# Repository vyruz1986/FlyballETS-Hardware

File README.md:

## FlyballETS-Hardware

The FlyballETS-Hardware project is a subproject of the [Flyball ETS project](https://www.sparkydevices.com/tag/flyball-ets/).
It contains the designs for the electronic hardware which is required to build the Flyball-ETS project.

## Design Files

The design files are in KiCAD format, and consist of several files:
* FlyballETS-Board.sch/kicad_pcb: Schematic and board file for the PCB of Flyball ETS
* FlyballETS-Board-BOM.txt: Bill of materials used to know which components to order and where to solder them on the board

These files can be used by people who want to improve or change the design.

## Export Files
`Exports/FlyballETS-Board-BRD/SCH.png` are picture exports of the design files so people can view them without needing to install EAGLE

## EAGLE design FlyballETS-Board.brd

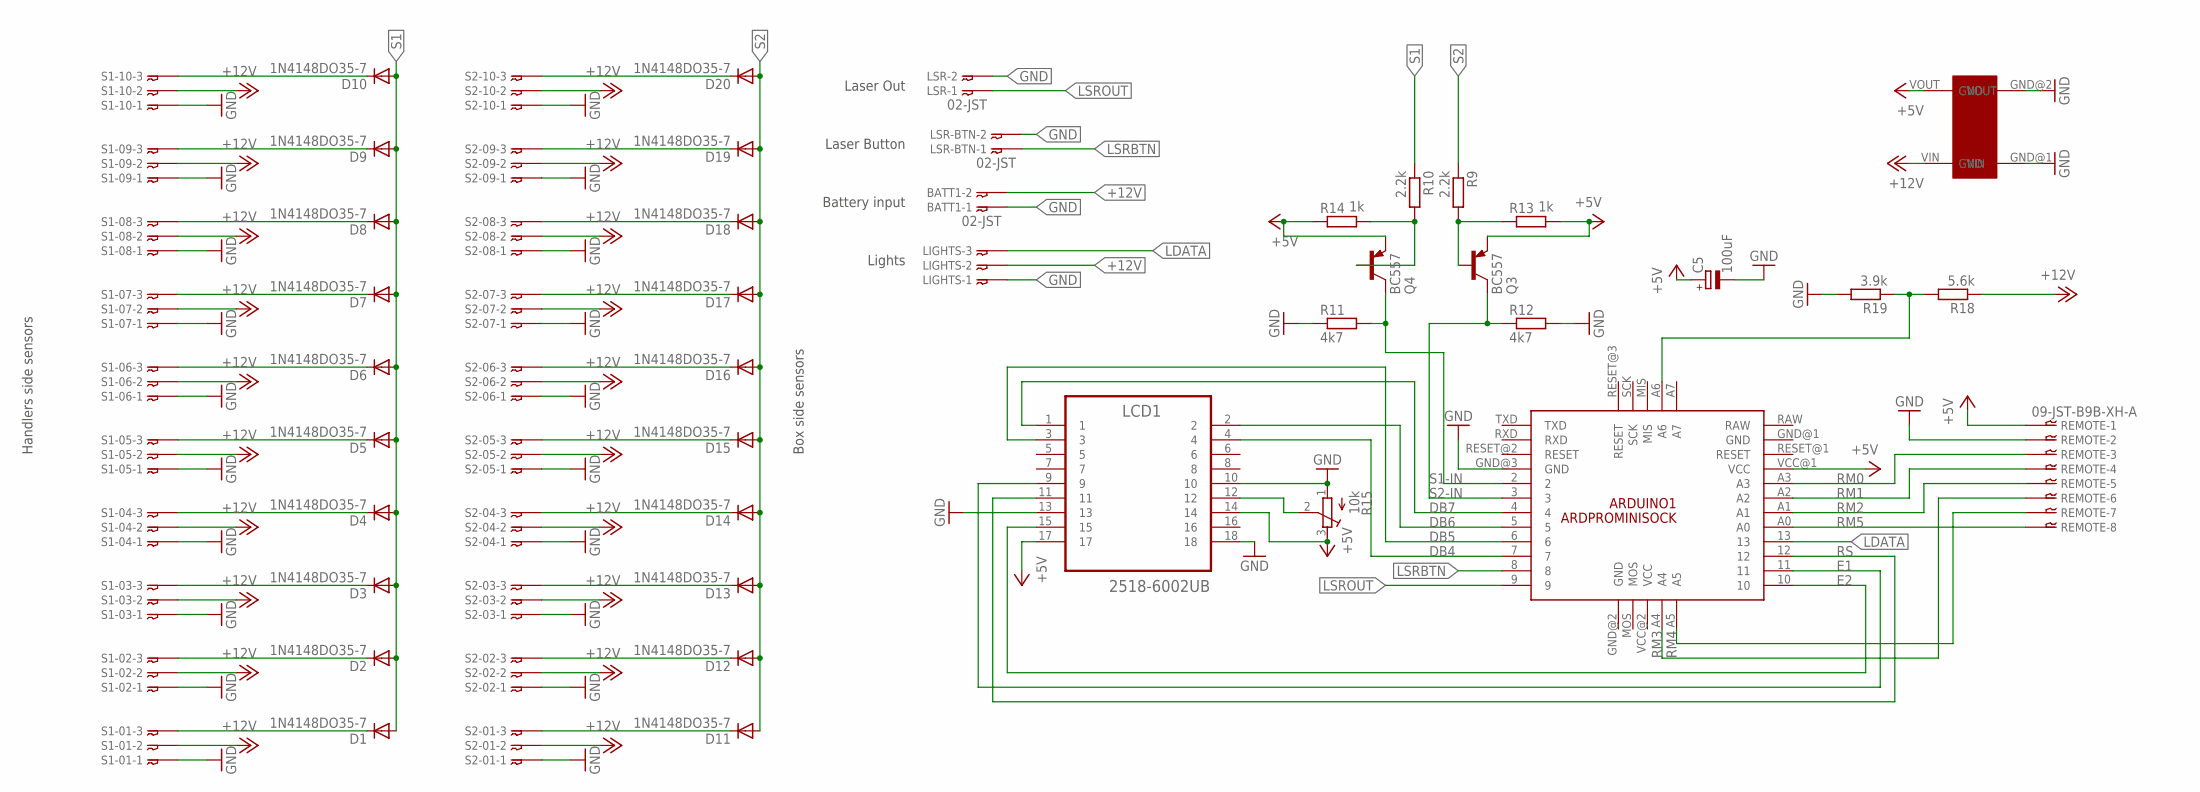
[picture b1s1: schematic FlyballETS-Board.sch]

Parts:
ARDUINO1: ARDPROMINISOCK
BATT1: 02-JST; B2B-XH
C5: 100uF; E2,5-6E
D1, D2, D3, D4, D5, D6, D7, D8, D9, D10, D11, D12, D13, D14, D15, D16, D17, D18, D19, D20: 1N4148DO35-7; DO35-7
LCD1: 2518-6002UB; 3M_2518-6002UB
LIGHTS: 03-JST-B3B-XH-A; B3B-XH
LSR: 02-JST; B2B-XH
LSR-BTN: 02-JST; B2B-XH
Q3, Q4: BC557; TO92
R9, R10: 2.2k; 0207/10
R11, R12: 4k7; 0207/10
R13, R14: 1k; 0207/10
R15: 10k; RTRIM3339P
R18: 5.6k; 0207/10
R19: 3.9k; 0207/10
REMOTE: 09-JST-B9B-XH-A; B9B-XH
S1-01, S1-02, S1-03, S1-04, S1-05, S1-06, S1-07, S1-08, S1-09, S1-10, S2-01, S2-02, S2-03, S2-04, S2-05, S2-06, S2-07, S2-08, S2-09, S2-10: 03-JST-B3B-XH-A; B3B-XH
U$2: LM2596-BOARD

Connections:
+5V: ARDUINO1.VCC@1 (VCC), C5.+, LCD1.14, LCD1.17, Q3.1 (E), Q4.1 (E), R13.2, R14.1, R15.3 (E), REMOTE.P$1, U$2.VOUT
+12V: BATT1.P$2, LIGHTS.P$2, R18.1, S1-01.P$2, S1-02.P$2, S1-03.P$2, S1-04.P$2, S1-05.P$2, S1-06.P$2, S1-07.P$2, S1-08.P$2, S1-09.P$2, S1-10.P$2, S2-01.P$2, S2-02.P$2, S2-03.P$2, S2-04.P$2, S2-05.P$2, S2-06.P$2, S2-07.P$2, S2-08.P$2, S2-09.P$2, S2-10.P$2, U$2.VIN
DB4: ARDUINO1.7, LCD1.4
DB5: ARDUINO1.6, LCD1.3
DB6: ARDUINO1.5, LCD1.2
DB7: ARDUINO1.4, LCD1.1
E1: ARDUINO1.11, LCD1.9
E2: ARDUINO1.10, LCD1.15
GND: ARDUINO1.GND@3 (GND), BATT1.P$1, C5.-, LCD1.10, LCD1.13, LCD1.18, LIGHTS.P$1, LSR.P$2, LSR-BTN.P$2, R11.1, R12.2, R15.1 (A), R19.2, REMOTE.P$2, S1-01.P$1, S1-02.P$1, S1-03.P$1, S1-04.P$1, S1-05.P$1, S1-06.P$1, S1-07.P$1, S1-08.P$1, S1-09.P$1, S1-10.P$1, S2-01.P$1, S2-02.P$1, S2-03.P$1, S2-04.P$1, S2-05.P$1, S2-06.P$1, S2-07.P$1, S2-08.P$1, S2-09.P$1, S2-10.P$1, U$2.GND@1 (GND), U$2.GND@2 (GND)
LDATA: ARDUINO1.13, LIGHTS.P$3
LSRBTN: ARDUINO1.8, LSR-BTN.P$1
LSROUT: ARDUINO1.9, LSR.P$1
unnamed: Q3.2 (B), R9.2, R13.1
unnamed: Q4.2 (B), R10.2, R14.2
unnamed: LCD1.12, R15.2 (S)
unnamed: D10.C, S1-10.P$3
unnamed: D9.C, S1-09.P$3
unnamed: D8.C, S1-08.P$3
unnamed: D7.C, S1-07.P$3
unnamed: D6.C, S1-06.P$3
unnamed: D5.C, S1-05.P$3
unnamed: D4.C, S1-04.P$3
unnamed: D3.C, S1-03.P$3
unnamed: D2.C, S1-02.P$3
unnamed: D1.C, S1-01.P$3
unnamed: D20.C, S2-10.P$3
unnamed: D19.C, S2-09.P$3
unnamed: D18.C, S2-08.P$3
unnamed: D17.C, S2-07.P$3
unnamed: D16.C, S2-06.P$3
unnamed: D15.C, S2-05.P$3
unnamed: D14.C, S2-04.P$3
unnamed: D13.C, S2-03.P$3
unnamed: D12.C, S2-02.P$3
unnamed: D11.C, S2-01.P$3
RM0: ARDUINO1.A3, REMOTE.P$3
RM1: ARDUINO1.A2, REMOTE.P$4
RM2: ARDUINO1.A1, REMOTE.P$5
RM3: ARDUINO1.A4, REMOTE.P$6
RM4: ARDUINO1.A5, REMOTE.P$7
RM5: ARDUINO1.A0, REMOTE.P$8
RS: ARDUINO1.12, LCD1.11
S1: D1.A, D2.A, D3.A, D4.A, D5.A, D6.A, D7.A, D8.A, D9.A, D10.A, R10.1
S1-IN: ARDUINO1.2, Q4.3 (C), R11.2
S2: D11.A, D12.A, D13.A, D14.A, D15.A, D16.A, D17.A, D18.A, D19.A, D20.A, R9.1
S2-IN: ARDUINO1.3, Q3.3 (C), R12.1
VSENS: ARDUINO1.A6, R18.2, R19.1

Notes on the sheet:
Battery input
Handlers side sensors
Box side sensors
Laser Out
Laser Button
Lights

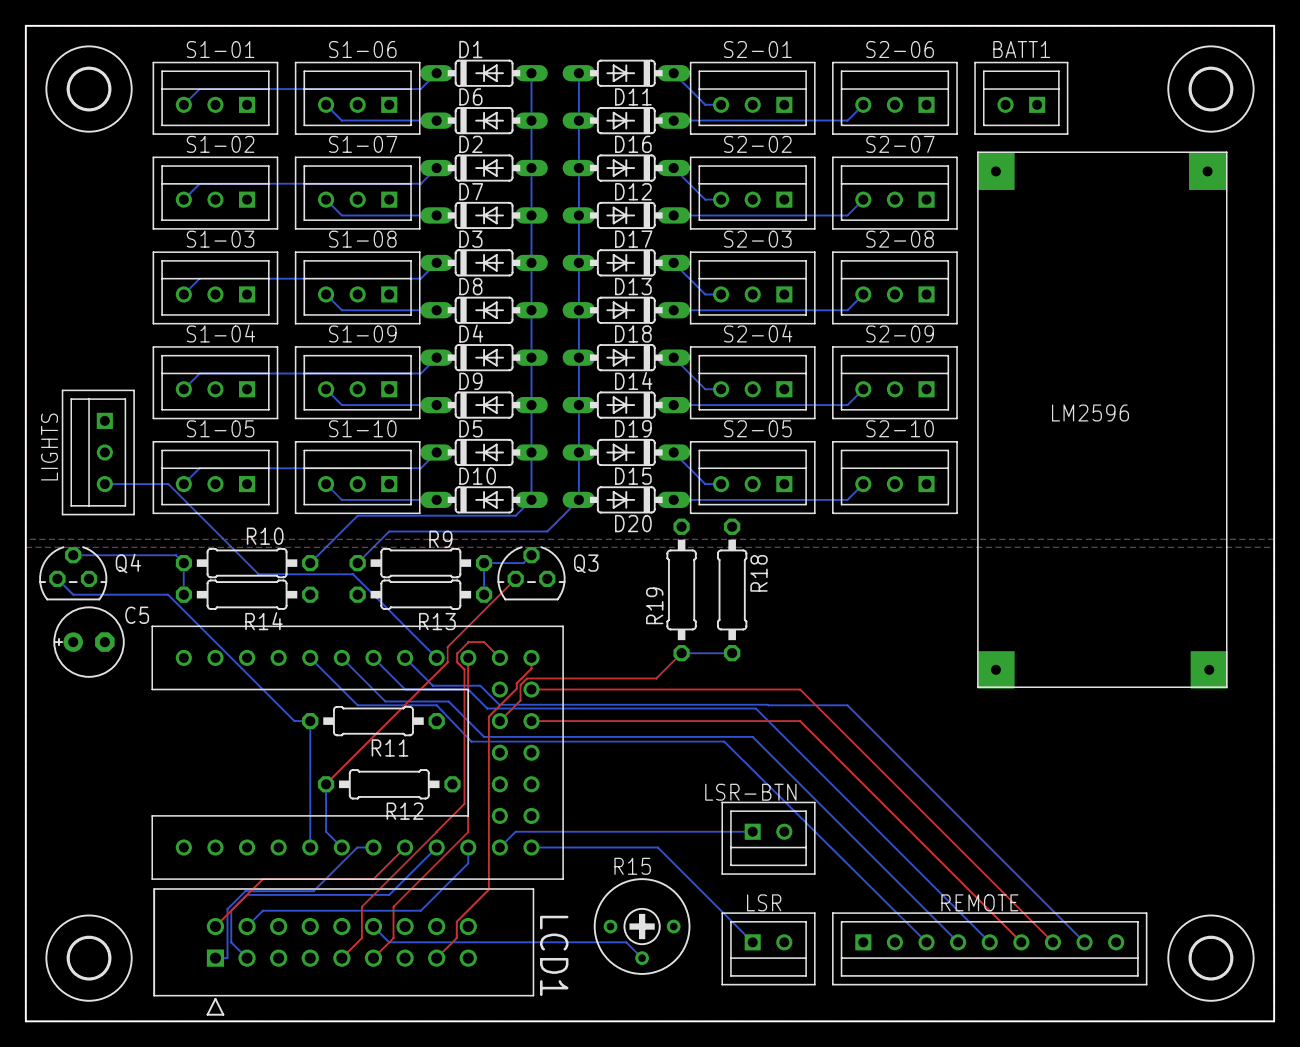
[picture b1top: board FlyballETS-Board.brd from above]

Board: 2 copper layers, 100.3 x 80.0 mm, 64 parts (0 on the bottom side), 47 nets.

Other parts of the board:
U$1, U$3, U$4, U$5: 3,2

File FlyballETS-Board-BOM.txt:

Partlist exported from C:/Workspaces/personal/FlyballETS-Hardware/FlyballETS-Board.sch at 25/10/2017 10:56

Part     Value           Device          Package        Description                          
ARDUINO1 ARDPROMINISOCK  ARDPROMINISOCK  ARDPROMINISOCK                                      
BATT1    02-JST          02-JST          B2B-XH         JST CONNECTOR                        
C5       100uF           CPOL-EUE2,5-6E  E2,5-6E        POLARIZED CAPACITOR, European symbol 
D1       1N4148DO35-7    1N4148DO35-7    DO35-7         DIODE                                
D2       1N4148DO35-7    1N4148DO35-7    DO35-7         DIODE                                
D3       1N4148DO35-7    1N4148DO35-7    DO35-7         DIODE                                
D4       1N4148DO35-7    1N4148DO35-7    DO35-7         DIODE                                
D5       1N4148DO35-7    1N4148DO35-7    DO35-7         DIODE                                
D6       1N4148DO35-7    1N4148DO35-7    DO35-7         DIODE                                
D7       1N4148DO35-7    1N4148DO35-7    DO35-7         DIODE                                
D8       1N4148DO35-7    1N4148DO35-7    DO35-7         DIODE                                
D9       1N4148DO35-7    1N4148DO35-7    DO35-7         DIODE                                
D10      1N4148DO35-7    1N4148DO35-7    DO35-7         DIODE                                
D11      1N4148DO35-7    1N4148DO35-7    DO35-7         DIODE                                
D12      1N4148DO35-7    1N4148DO35-7    DO35-7         DIODE                                
D13      1N4148DO35-7    1N4148DO35-7    DO35-7         DIODE                                
D14      1N4148DO35-7    1N4148DO35-7    DO35-7         DIODE                                
D15      1N4148DO35-7    1N4148DO35-7    DO35-7         DIODE                                
D16      1N4148DO35-7    1N4148DO35-7    DO35-7         DIODE                                
D17      1N4148DO35-7    1N4148DO35-7    DO35-7         DIODE                                
D18      1N4148DO35-7    1N4148DO35-7    DO35-7         DIODE                                
D19      1N4148DO35-7    1N4148DO35-7    DO35-7         DIODE                                
D20      1N4148DO35-7    1N4148DO35-7    DO35-7         DIODE                                
LCD1     2518-6002UB     2518-6002UB     3M_2518-6002UB                                      
LIGHTS   03-JST-B3B-XH-A 03-JST-B3B-XH-A B3B-XH         JST CONNECTOR                        
LSR      02-JST          02-JST          B2B-XH         JST CONNECTOR                        
LSR-BTN  02-JST          02-JST          B2B-XH         JST CONNECTOR                        
Q3       BC557           BC557           TO92           PNP Transistor                       
Q4       BC557           BC557           TO92           PNP Transistor                       
R9       2.2k            R-EU_0207/10    0207/10        RESISTOR, European symbol            
R10      2.2k            R-EU_0207/10    0207/10        RESISTOR, European symbol            
R11      4k7             R-EU_0207/10    0207/10        RESISTOR, European symbol            
R12      4k7             R-EU_0207/10    0207/10        RESISTOR, European symbol            
R13      1k              R-EU_0207/10    0207/10        RESISTOR, European symbol            
R14      1k              R-EU_0207/10    0207/10        RESISTOR, European symbol            
R15      10k             R-TRIMM3339P    RTRIM3339P     Trimm resistor                       
R18      5.6k            R-EU_0207/10    0207/10        RESISTOR, European symbol            
R19      3.9k            R-EU_0207/10    0207/10        RESISTOR, European symbol            
REMOTE   09-JST-B9B-XH-A 09-JST-B9B-XH-A B9B-XH         JST CONNECTOR                        
S1-01    03-JST-B3B-XH-A 03-JST-B3B-XH-A B3B-XH         JST CONNECTOR                        
S1-02    03-JST-B3B-XH-A 03-JST-B3B-XH-A B3B-XH         JST CONNECTOR                        
S1-03    03-JST-B3B-XH-A 03-JST-B3B-XH-A B3B-XH         JST CONNECTOR                        
S1-04    03-JST-B3B-XH-A 03-JST-B3B-XH-A B3B-XH         JST CONNECTOR                        
S1-05    03-JST-B3B-XH-A 03-JST-B3B-XH-A B3B-XH         JST CONNECTOR                        
S1-06    03-JST-B3B-XH-A 03-JST-B3B-XH-A B3B-XH         JST CONNECTOR                        
S1-07    03-JST-B3B-XH-A 03-JST-B3B-XH-A B3B-XH         JST CONNECTOR                        
S1-08    03-JST-B3B-XH-A 03-JST-B3B-XH-A B3B-XH         JST CONNECTOR                        
S1-09    03-JST-B3B-XH-A 03-JST-B3B-XH-A B3B-XH         JST CONNECTOR                        
S1-10    03-JST-B3B-XH-A 03-JST-B3B-XH-A B3B-XH         JST CONNECTOR                        
S2-01    03-JST-B3B-XH-A 03-JST-B3B-XH-A B3B-XH         JST CONNECTOR                        
S2-02    03-JST-B3B-XH-A 03-JST-B3B-XH-A B3B-XH         JST CONNECTOR                        
S2-03    03-JST-B3B-XH-A 03-JST-B3B-XH-A B3B-XH         JST CONNECTOR                        
S2-04    03-JST-B3B-XH-A 03-JST-B3B-XH-A B3B-XH         JST CONNECTOR                        
S2-05    03-JST-B3B-XH-A 03-JST-B3B-XH-A B3B-XH         JST CONNECTOR                        
S2-06    03-JST-B3B-XH-A 03-JST-B3B-XH-A B3B-XH         JST CONNECTOR                        
S2-07    03-JST-B3B-XH-A 03-JST-B3B-XH-A B3B-XH         JST CONNECTOR                        
S2-08    03-JST-B3B-XH-A 03-JST-B3B-XH-A B3B-XH         JST CONNECTOR                        
S2-09    03-JST-B3B-XH-A 03-JST-B3B-XH-A B3B-XH         JST CONNECTOR                        
S2-10    03-JST-B3B-XH-A 03-JST-B3B-XH-A B3B-XH         JST CONNECTOR                        
U$2      LM2596-BOARD    LM2596-BOARD    LM2596-BOARD

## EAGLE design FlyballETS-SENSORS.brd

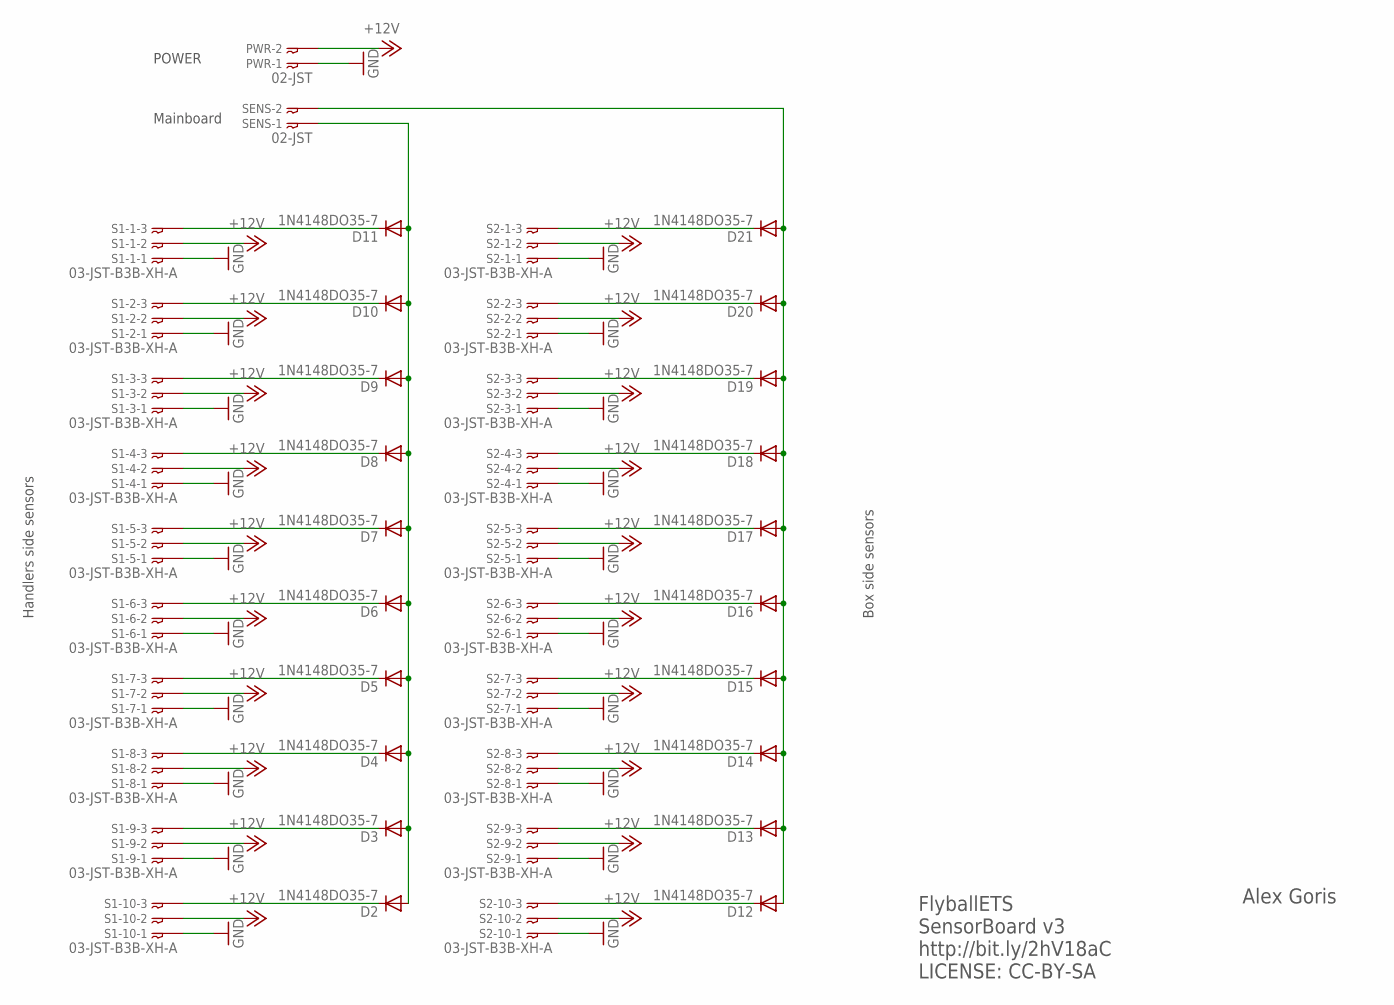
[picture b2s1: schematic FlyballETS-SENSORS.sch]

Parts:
D2, D3, D4, D5, D6, D7, D8, D9, D10, D11, D12, D13, D14, D15, D16, D17, D18, D19, D20, D21: 1N4148DO35-7; DO35-7
PWR: 02-JST; B2B-XH
S1-1, S1-2, S1-3, S1-4, S1-5, S1-6, S1-7, S1-8, S1-9, S1-10, S2-1, S2-2, S2-3, S2-4, S2-5, S2-6, S2-7, S2-8, S2-9, S2-10: 03-JST-B3B-XH-A; B3B-XH
SENS: 02-JST; B2B-XH

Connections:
+12V: PWR.P$2, S1-1.P$2, S1-2.P$2, S1-3.P$2, S1-4.P$2, S1-5.P$2, S1-6.P$2, S1-7.P$2, S1-8.P$2, S1-9.P$2, S1-10.P$2, S2-1.P$2, S2-2.P$2, S2-3.P$2, S2-4.P$2, S2-5.P$2, S2-6.P$2, S2-7.P$2, S2-8.P$2, S2-9.P$2, S2-10.P$2
GND: PWR.P$1, S1-1.P$1, S1-2.P$1, S1-3.P$1, S1-4.P$1, S1-5.P$1, S1-6.P$1, S1-7.P$1, S1-8.P$1, S1-9.P$1, S1-10.P$1, S2-1.P$1, S2-2.P$1, S2-3.P$1, S2-4.P$1, S2-5.P$1, S2-6.P$1, S2-7.P$1, S2-8.P$1, S2-9.P$1, S2-10.P$1
unnamed: D11.C, S1-1.P$3
unnamed: D10.C, S1-2.P$3
unnamed: D9.C, S1-3.P$3
unnamed: D8.C, S1-4.P$3
unnamed: D7.C, S1-5.P$3
unnamed: D6.C, S1-6.P$3
unnamed: D5.C, S1-7.P$3
unnamed: D4.C, S1-8.P$3
unnamed: D3.C, S1-9.P$3
unnamed: D2.C, S1-10.P$3
unnamed: D21.C, S2-1.P$3
unnamed: D20.C, S2-2.P$3
unnamed: D19.C, S2-3.P$3
unnamed: D18.C, S2-4.P$3
unnamed: D17.C, S2-5.P$3
unnamed: D16.C, S2-6.P$3
unnamed: D15.C, S2-7.P$3
unnamed: D14.C, S2-8.P$3
unnamed: D13.C, S2-9.P$3
unnamed: D12.C, S2-10.P$3
S1: D12.A, D13.A, D14.A, D15.A, D16.A, D17.A, D18.A, D19.A, D20.A, D21.A, SENS.P$2
S2: D2.A, D3.A, D4.A, D5.A, D6.A, D7.A, D8.A, D9.A, D10.A, D11.A, SENS.P$1

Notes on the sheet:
POWER
Mainboard
Handlers side sensors
Box side sensors
FlyballETS SensorBoard v3 http://bit.ly/2hV18aC LICENSE: CC-BY-SA
Alex Goris

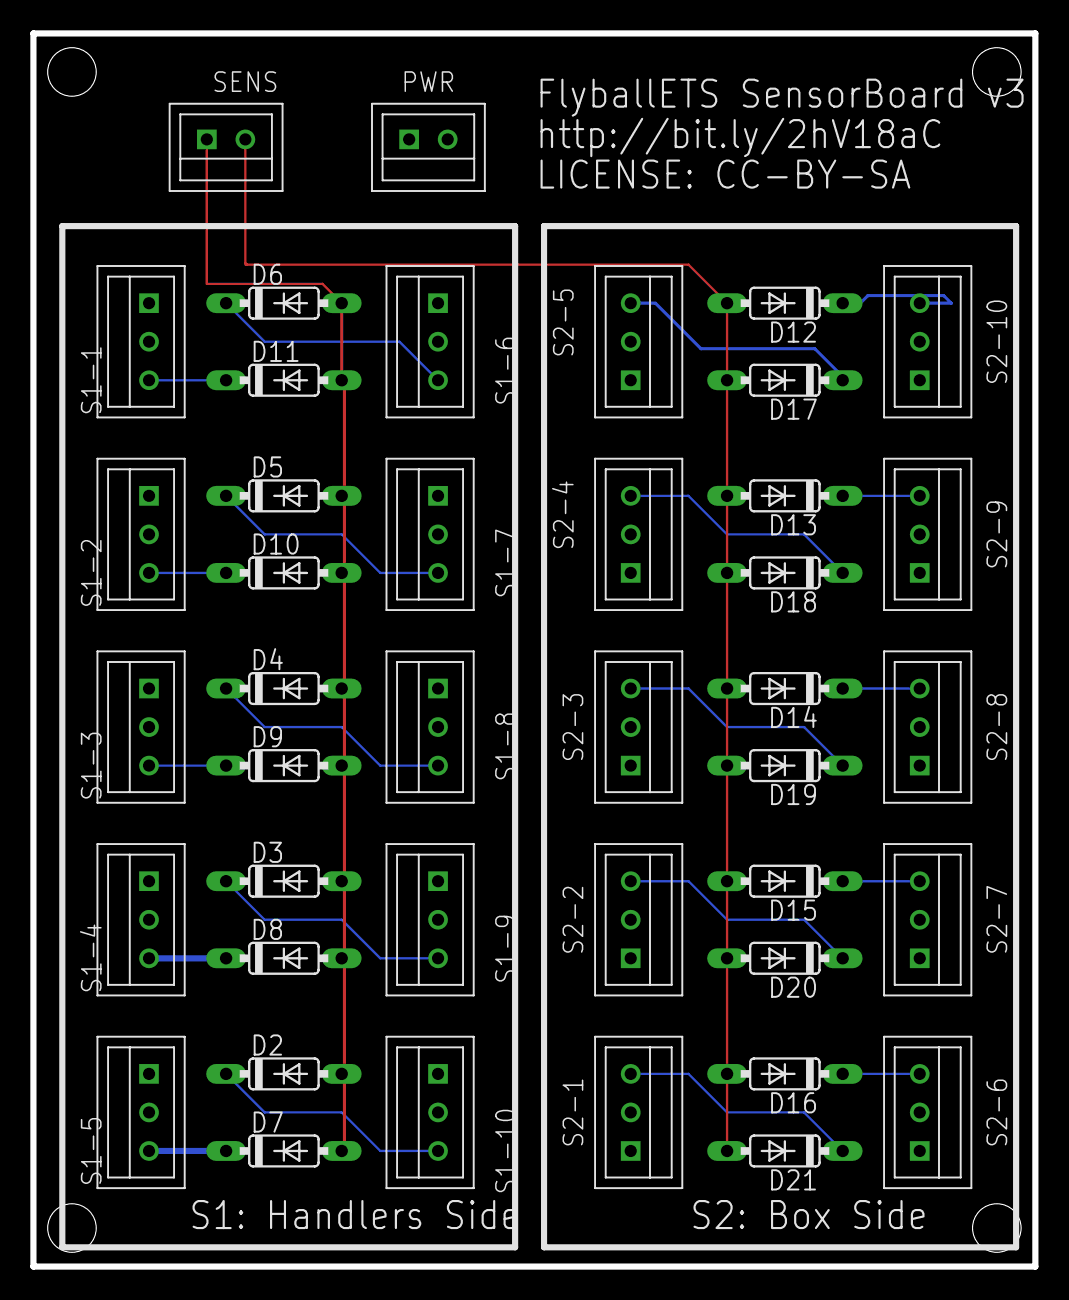
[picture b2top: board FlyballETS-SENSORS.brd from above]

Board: 2 copper layers, 66.0 x 81.3 mm, 43 parts (0 on the bottom side), 24 nets.

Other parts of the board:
U$1: A5L-LOC

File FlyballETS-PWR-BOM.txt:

Partlist exported from C:/Users/Alex/Documents/eagle/FlyballETS-Hardware/FlyballETS-PWR.sch at 30/12/2015 17:42

Part    Value           Device          Package      Description               
BATT    02-JST-B2B-XH-A 02-JST-B2B-XH-A B2B-XH       JST CONNECTOR             
LCDBL   02-JST-B2B-XH-A 02-JST-B2B-XH-A B2B-XH       JST CONNECTOR             
LIGHTS  03-JST-B3B-XH-A 03-JST-B3B-XH-A B3B-XH       JST CONNECTOR             
MBD     03-JST-B3B-XH-A 03-JST-B3B-XH-A B3B-XH       JST CONNECTOR             
R1      70k             R-EU_0204/5     0204/5       RESISTOR, European symbol 
R2      50k             R-EU_0204/5     0204/5       RESISTOR, European symbol 
SENSORS 02-JST-B2B-XH-A 02-JST-B2B-XH-A B2B-XH       JST CONNECTOR             
U$1     LM2596-BOARD    LM2596-BOARD    LM2596-BOARD

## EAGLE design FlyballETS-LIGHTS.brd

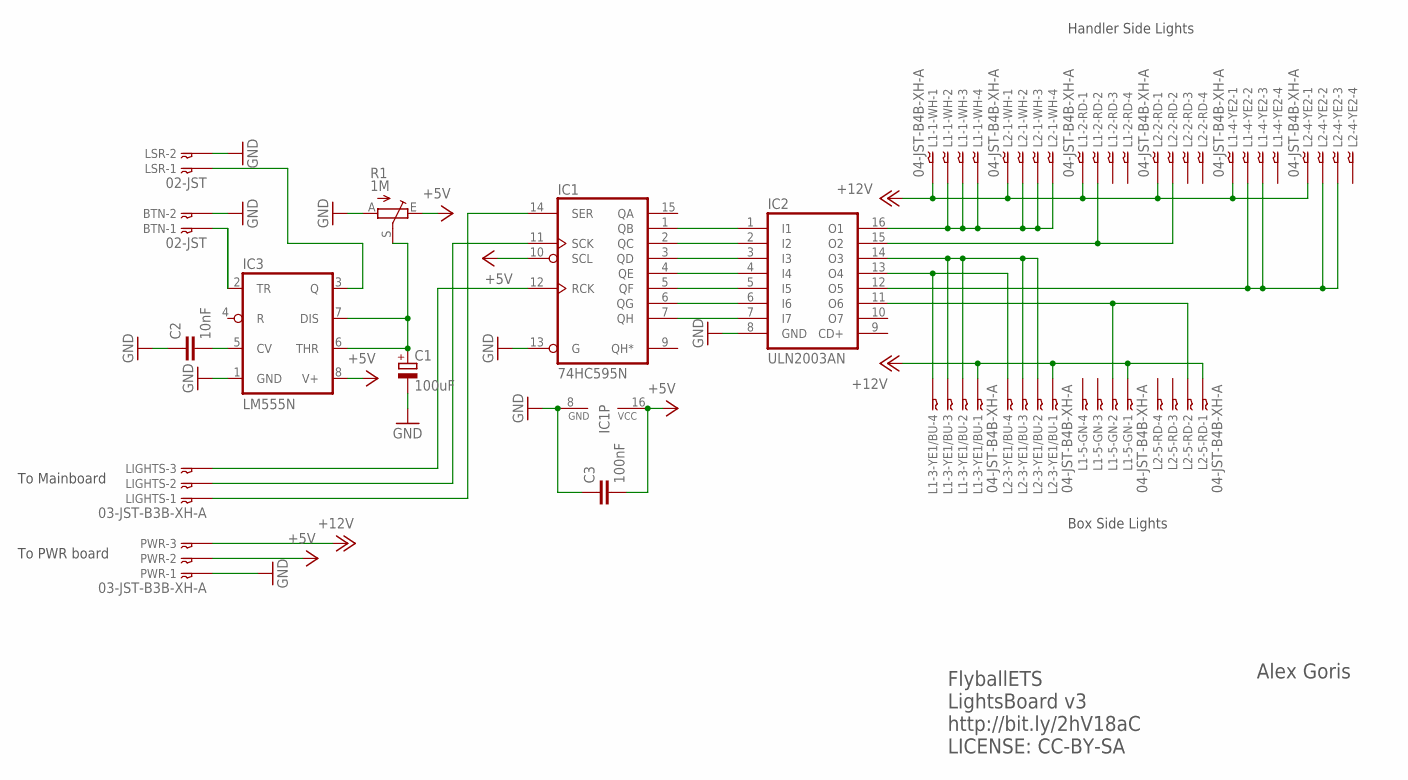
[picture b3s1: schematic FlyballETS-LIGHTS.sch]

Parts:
BTN: 02-JST; B2B-XH
C1: 100uF; E2,5-7
C2: 10nF; C050-030X075
C3: 100nF; C050-030X075
IC1: 74HC595N; DIL16
IC2: ULN2003AN; DIL16
IC3: LM555N; DIL08
L1-1-WH, L1-2-RD, L1-3-YE1/BU, L1-4-YE2, L1-5-GN, L2-1-WH, L2-2-RD, L2-3-YE1/BU, L2-4-YE2, L2-5-RD: 04-JST-B4B-XH-A; B4B-XH
LIGHTS: 03-JST-B3B-XH-A; B3B-XH
LSR: 02-JST; B2B-XH
PWR: 03-JST-B3B-XH-A; B3B-XH
R1: 1M; B25P

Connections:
+5V: C3.2, IC1.10 (SCL), IC1.16 (VCC), IC3.8 (V+), PWR.P$2, R1.E
+12V: L1-1-WH.P$1, L1-2-RD.P$1, L1-3-YE1/BU.P$1, L1-4-YE2.P$1, L1-5-GN.P$1, L2-1-WH.P$1, L2-2-RD.P$1, L2-3-YE1/BU.P$1, L2-4-YE2.P$1, L2-5-RD.P$1, PWR.P$3
GND: BTN.P$2, C1.-, C2.1, C3.1, IC1.8 (GND), IC1.13 (G), IC2.8 (GND), IC3.1 (GND), LSR.P$2, PWR.P$1, R1.A
unnamed: IC1.14 (SER), LIGHTS.P$1
unnamed: IC1.11 (SCK), LIGHTS.P$2
unnamed: IC1.12 (RCK), LIGHTS.P$3
unnamed: IC1.1 (QB), IC2.1 (I1)
unnamed: IC1.2 (QC), IC2.2 (I2)
unnamed: IC1.3 (QD), IC2.3 (I3)
unnamed: IC1.4 (QE), IC2.4 (I4)
unnamed: IC1.5 (QF), IC2.5 (I5)
unnamed: IC1.6 (QG), IC2.6 (I6)
unnamed: IC1.7 (QH), IC2.7 (I7)
unnamed: C1.+, IC3.6 (THR), IC3.7 (DIS), R1.S
unnamed: C2.2, IC3.5 (CV)
unnamed: IC2.16 (O1), L1-1-WH.P$2, L1-1-WH.P$3, L1-1-WH.P$4, L2-1-WH.P$2, L2-1-WH.P$3, L2-1-WH.P$4
unnamed: BTN.P$1, IC3.2 (TR)
unnamed: IC3.3 (Q), LSR.P$1
unnamed: IC2.15 (O2), L1-2-RD.P$2, L2-2-RD.P$2
unnamed: IC2.14 (O3), L1-3-YE1/BU.P$2, L1-3-YE1/BU.P$3, L2-3-YE1/BU.P$2, L2-3-YE1/BU.P$3
unnamed: IC2.13 (O4), L1-3-YE1/BU.P$4, L2-3-YE1/BU.P$4
unnamed: IC2.12 (O5), L1-4-YE2.P$2, L1-4-YE2.P$3, L2-4-YE2.P$2, L2-4-YE2.P$3
unnamed: IC2.11 (O6), L1-5-GN.P$2, L2-5-RD.P$2

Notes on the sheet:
To Mainboard
To PWR board
Handler Side Lights
Box Side Lights
FlyballETS LightsBoard v3 http://bit.ly/2hV18aC LICENSE: CC-BY-SA
Alex Goris

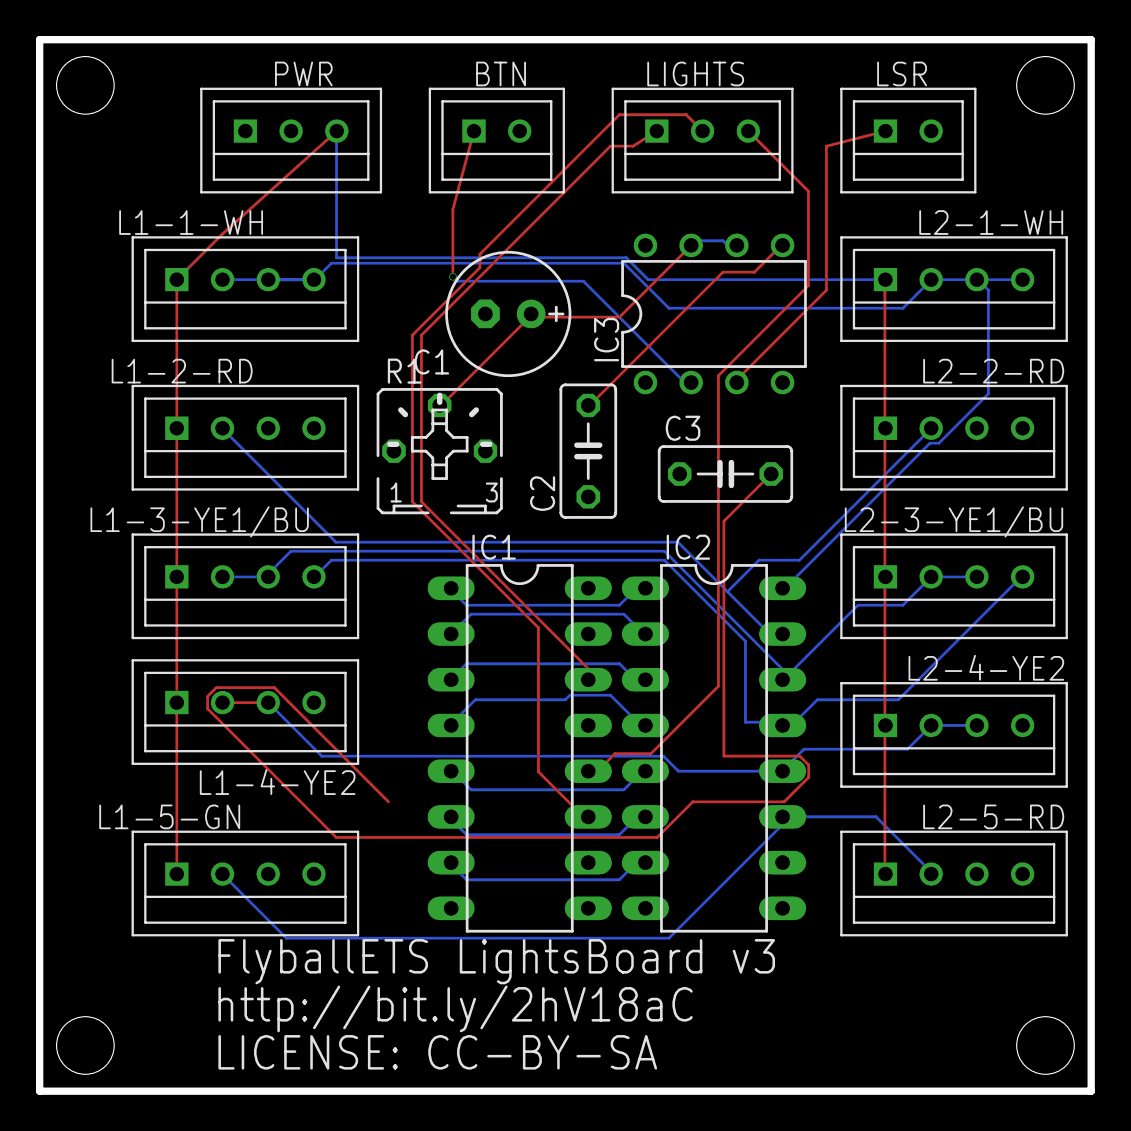
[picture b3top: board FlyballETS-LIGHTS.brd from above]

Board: 2 copper layers, 58.4 x 58.4 mm, 22 parts (0 on the bottom side), 23 nets.

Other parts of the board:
U$1: A4L-LOC

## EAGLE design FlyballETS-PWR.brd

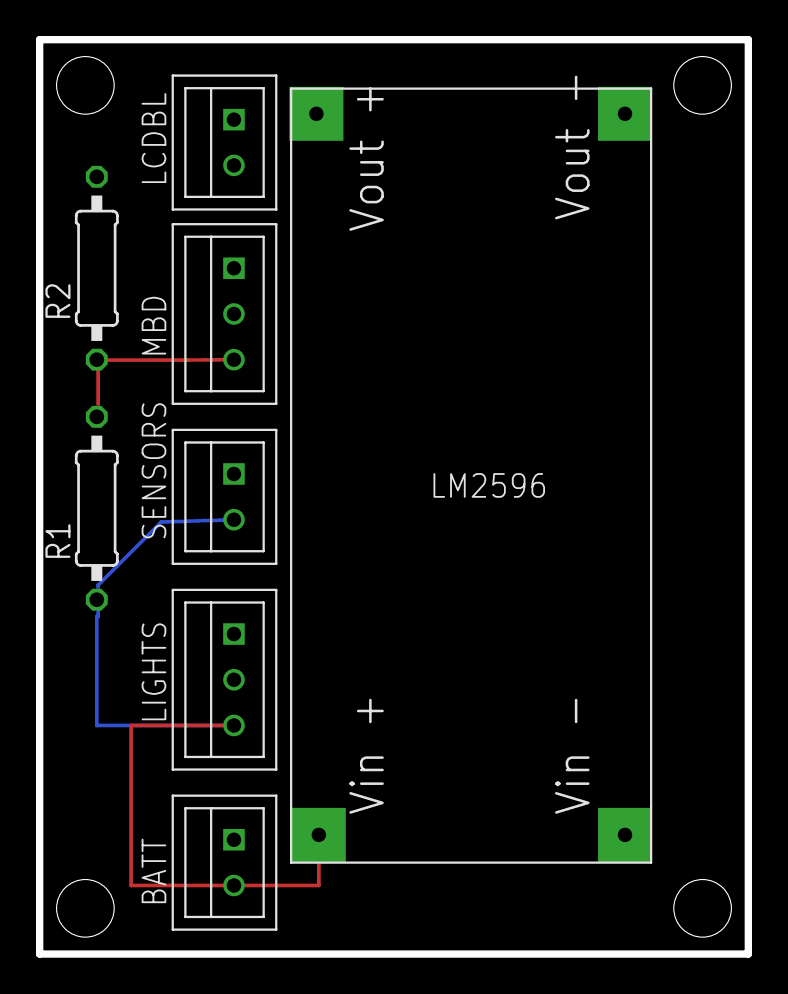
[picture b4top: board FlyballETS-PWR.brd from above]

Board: 2 copper layers, 39.4 x 50.8 mm, 9 parts (0 on the bottom side), 4 nets.

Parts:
BATT: 02-JST; B2B-XH
LCDBL: 02-JST; B2B-XH
LIGHTS: 03-JST-B3B-XH-A; B3B-XH
MBD: 03-JST-B3B-XH-A; B3B-XH
R1: 5.6k; 0207/10
R2: 3.9k; 0207/10
SENSORS: 02-JST; B2B-XH
U$1: LM2596-BOARD
U$2: A5L-LOC

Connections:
+5V: LCDBL.P$2, LIGHTS.P$2, MBD.P$2, U$1.VOUT
+12V: BATT.P$2, LIGHTS.P$3, R1.1, SENSORS.P$2, U$1.VIN
GND: BATT.P$1, LCDBL.P$1, LIGHTS.P$1, MBD.P$1, R2.2, SENSORS.P$1, U$1.GND@1, U$1.GND@2
unnamed: MBD.P$3, R1.2, R2.1

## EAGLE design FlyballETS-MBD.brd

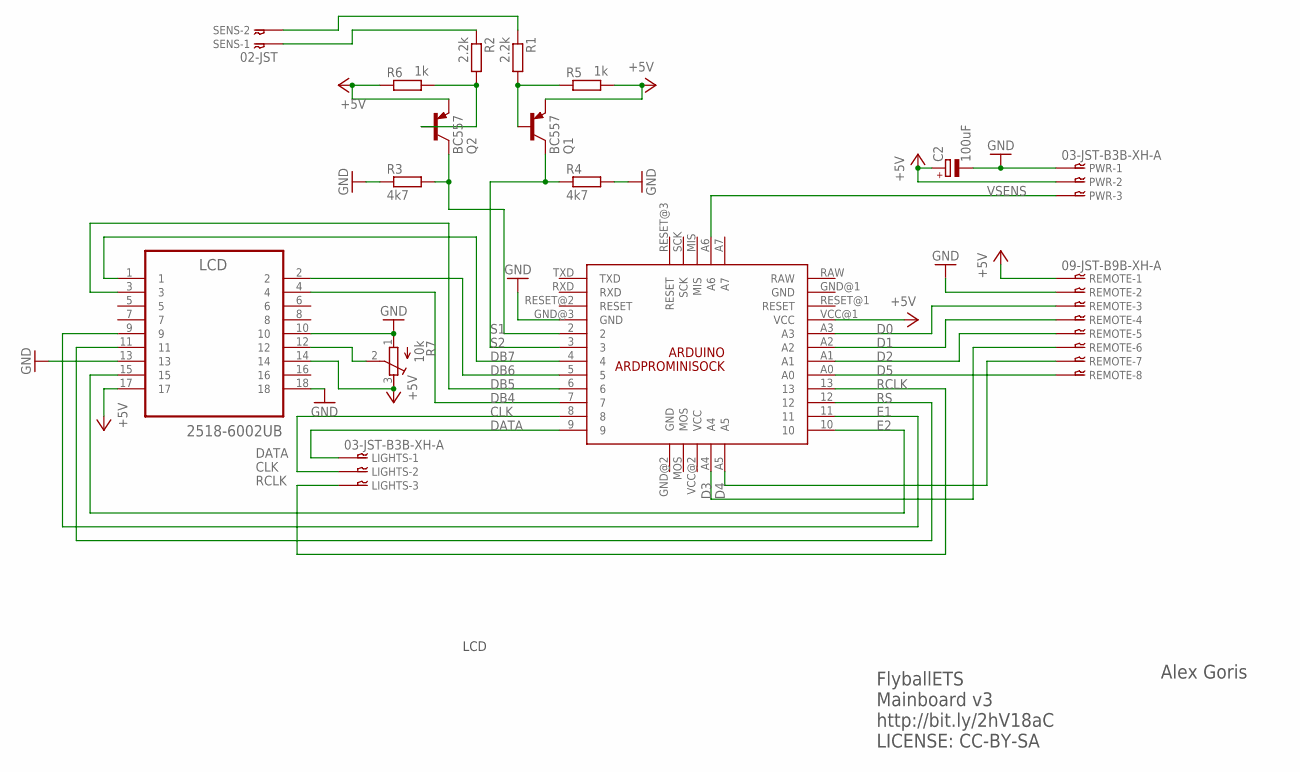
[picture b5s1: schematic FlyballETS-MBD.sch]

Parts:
ARDUINO: ARDPROMINISOCK
C2: 100uF; E2,5-6E
LCD: 2518-6002UB; 3M_2518-6002UB
LIGHTS: 03-JST-B3B-XH-A; B3B-XH
PWR: 03-JST-B3B-XH-A; B3B-XH
Q1, Q2: BC557; TO92
R1, R2: 2.2k; 0207/10
R3, R4: 4k7; 0207/10
R5, R6: 1k; 0207/10
R7: 10k; RTRIM3339P
REMOTE: 09-JST-B9B-XH-A; B9B-XH
SENS: 02-JST; B2B-XH

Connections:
+5V: ARDUINO.VCC@1 (VCC), C2.+, LCD.14, LCD.17, PWR.P$2, Q1.1 (E), Q2.1 (E), R5.2, R6.1, R7.3 (E), REMOTE.P$1
CLK: ARDUINO.8, LIGHTS.P$2
D0: ARDUINO.A3, REMOTE.P$3
D1: ARDUINO.A2, REMOTE.P$4
D2: ARDUINO.A1, REMOTE.P$5
D3: ARDUINO.A4, REMOTE.P$6
D4: ARDUINO.A5, REMOTE.P$7
D5: ARDUINO.A0, REMOTE.P$8
DATA: ARDUINO.9, LIGHTS.P$1
DB4: ARDUINO.7, LCD.4
DB5: ARDUINO.6, LCD.3
DB6: ARDUINO.5, LCD.2
DB7: ARDUINO.4, LCD.1
E1: ARDUINO.11, LCD.9
E2: ARDUINO.10, LCD.15
GND: ARDUINO.GND@3 (GND), C2.-, LCD.10, LCD.13, LCD.18, PWR.P$1, R3.1, R4.2, R7.1 (A), REMOTE.P$2
unnamed: R1.1, SENS.P$2
unnamed: R2.1, SENS.P$1
unnamed: Q1.2 (B), R1.2, R5.1
unnamed: Q2.2 (B), R2.2, R6.2
unnamed: LCD.12, R7.2 (S)
RCLK: ARDUINO.13, LIGHTS.P$3
RS: ARDUINO.12, LCD.11
S1: ARDUINO.2, Q2.3 (C), R3.2
S2: ARDUINO.3, Q1.3 (C), R4.1
VSENS: ARDUINO.A6, PWR.P$3

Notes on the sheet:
LCD
FlyballETS Mainboard v3 http://bit.ly/2hV18aC LICENSE: CC-BY-SA
Alex Goris

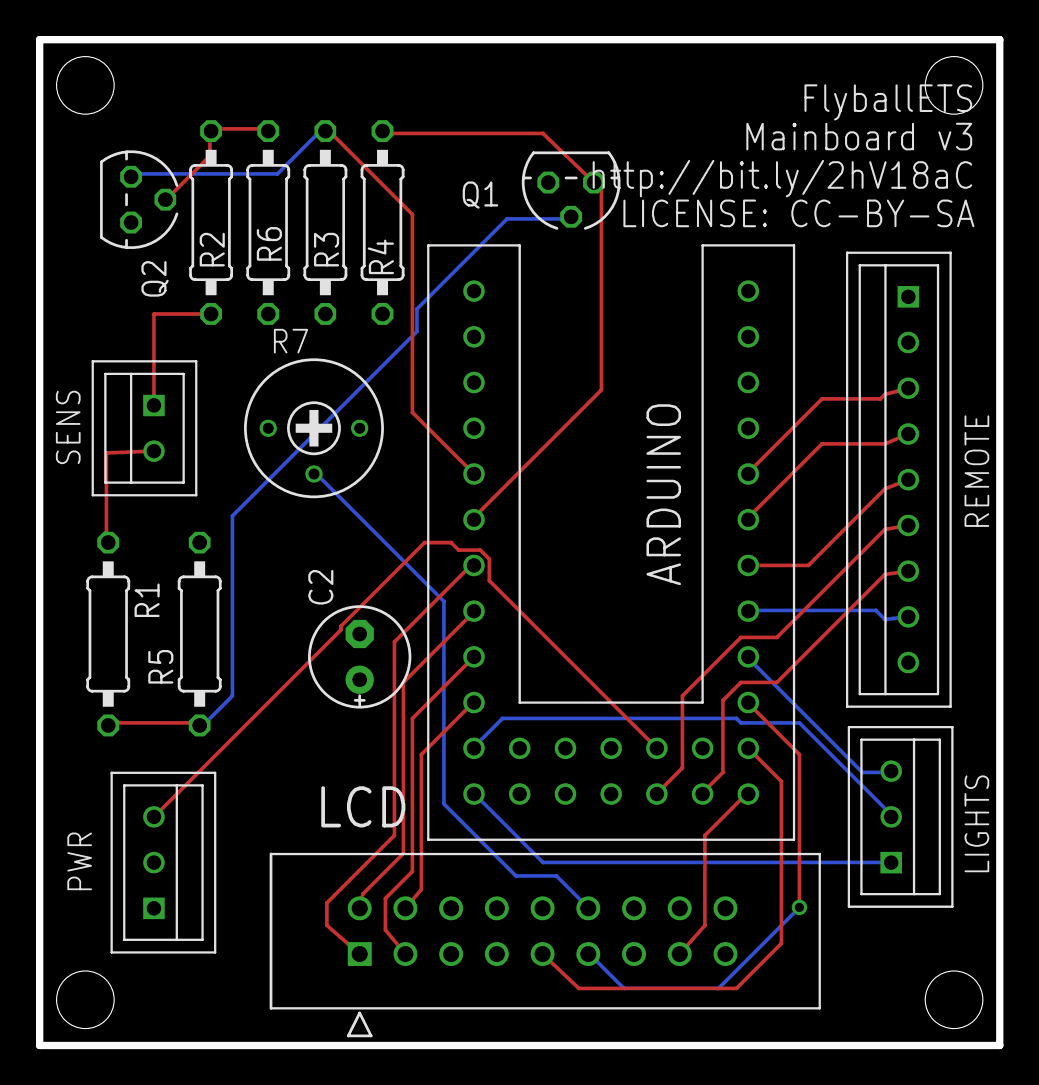
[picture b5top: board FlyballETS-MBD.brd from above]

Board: 2 copper layers, 53.3 x 55.9 mm, 17 parts (0 on the bottom side), 26 nets.

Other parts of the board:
U$1: A5L-LOC

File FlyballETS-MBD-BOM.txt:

Partlist exported from C:/Users/Alex/Documents/eagle/FlyballETS-Hardware/FlyballETS-MBD.sch at 30/12/2015 18:11

Part    Value           Device          Package        Description                          
ARDUINO ARDPROMINISOCK  ARDPROMINISOCK  ARDPROMINISOCK                                      
C2      100uF           CPOL-EUE2,5-6E  E2,5-6E        POLARIZED CAPACITOR, European symbol 
LCD     2518-6002UB     2518-6002UB     3M_2518-6002UB                                      
LIGHTS  03-JST-B3B-XH-A 03-JST-B3B-XH-A B3B-XH         JST CONNECTOR                        
PWR     03-JST-B3B-XH-A 03-JST-B3B-XH-A B3B-XH         JST CONNECTOR                        
Q1      BC557           BC557           TO92           PNP Transistor                       
Q2      BC557           BC557           TO92           PNP Transistor                       
R1      2.2k            R-EU_0207/10    0207/10        RESISTOR, European symbol            
R2      2.2k            R-EU_0207/10    0207/10        RESISTOR, European symbol            
R3      4k7             R-EU_0207/10    0207/10        RESISTOR, European symbol            
R4      4k7             R-EU_0207/10    0207/10        RESISTOR, European symbol            
R5      1k              R-EU_0207/10    0207/10        RESISTOR, European symbol            
R6      1k              R-EU_0207/10    0207/10        RESISTOR, European symbol            
R7      10k             R-TRIMM3339P    RTRIM3339P     Trimm resistor                       
REMOTE  09-JST          09-JST          B9B-XH         JST CONNECTOR                        
SENS    02-JST          02-JST          B2B-XH         JST CONNECTOR

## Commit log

2015-08-30 Cleaned up mainboard design
2015-08-31 Added power board files
2015-09-01 Removed leftover AutoRouter statistics file
2015-09-01 Updated readme to include PWR board description
2015-09-01 Updated drawings and added PNG exports
    - Added frames around drawings to make it look neater
    - Added PNG export files so people who don't have EAGLE can see
    everything
2015-09-05 Corrected unrouted airwire
    The SensorsBoard had an unrouted airwire, this has been corrected
2015-12-20 Mainboard v2
    - Changed connectors to use JST-XH type
    - For LCD screen use flatcable/ribboncable connector (2x9 pins)
    - Repositioned everything to allow for smaller board size (12% smaller)
2015-12-20 Ignore eagle autorouter files
2015-12-30 Minor updates + added BOMs
    - Updated to EAGLE 7.5.0
    - Added BOM text file exports
    - Renamed arduino socket on MBD board
2015-12-30 Incorrect capacitor value
    Changed 100nF to 100uF
2016-01-10 v2 release of remaining boards.
    - Lightsboard: Corrected swapped pin connections on L2 side and made
    smaller
    - Powerboard: Made smaller and added descriptions for LM2596 board
    - Sensorboard: Made smaller
    - All boards: Removed JST connector type names
2016-03-02 LightsBoard:Fix 74HC595 problems
    Closes #5
    - Added decoupling capacitor over GND and VCC of 74HC595
    - Added missing connection of 74HC595 pin10 to +5V
2016-03-13 Changed resistor values to more practical ones
    Changed R1 to 5.6kOhm, R2 to 3.9kOhm. These are common values in
    resistor assortments. Fixes #2
2016-05-10 Fixed several issues
    - Checked all mounting holes (fixes #1 )
    - Marked light colors on lights PCB (fixes #7 )
    - Swapped pins 2 and 3 on LIGHTS connected on PWR board (fixes #3 )
2017-08-12 Fixed JST XH pin numbering
    Updated bt_con-jst-xh.lbr library with swapped pin numbering.
    Updated all board designs with updated library so they have the
    connectors the right way around
    Fixes #4
2017-08-23 Added one board to rule them all :)
2017-09-18 First revision ESP32 board
    Switched to KiCAD for schematic & PCB design
    Remade board as it was with ARduino Pro Mini but put ESP32 socket in place.
    Also added connector for GPS module which I want to use for time synchronisation
2017-10-25 Final changes for v4 release
    - Corrected README
    - Removed obsolete schematics, boards and export pictures
    - Added export for schematic
2017-10-25 Updated README for kicad
    We switched from EAGLE to KiCAD so the readme should reflect this
2017-10-25 Updated gitignore for KiCAD
2017-10-25 Delete FlyballETS-HW.kicad_pcb-bak
    This file should not have been committed
2017-10-25 Delete FlyballETS-HW.bak
    This file should not have been committed
2017-10-25 Added KiCAD project file
2017-10-25 Fixed some prototype problems
    - Ran final DRC to fix copper planes (fixes #9)
    - R1 pad 1 was connected to GND (fixes #10)
    - Changed Q1 and Q2 to TO-92 inline wide footprint (fixes #11)
2017-10-25 Fixed 3D settings of remote connector
    It was rotated and offset incorrectly
2018-04-23 Corrected GPS connections
2018-06-20 Fixed smaller issues
    - Added mounting holes
    - Added 1000uF cap for Ws2811 lights
    - Added 300R resistor in WS2811 data line
    - Removed transistors to invert sensor signal (we need to use NPN, NO from now on)
2018-08-04 Final version
